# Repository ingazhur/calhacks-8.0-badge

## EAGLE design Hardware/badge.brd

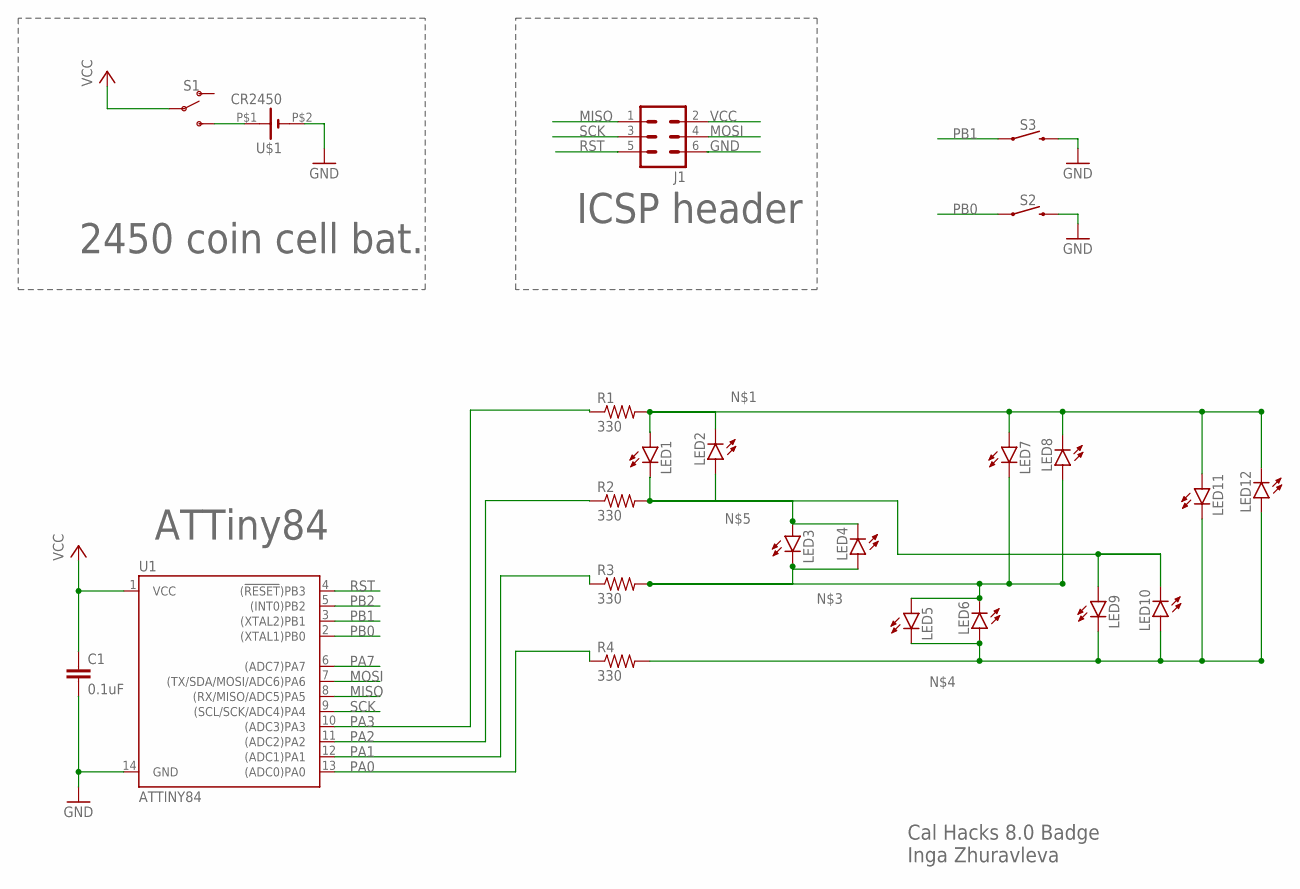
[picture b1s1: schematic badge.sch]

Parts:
C1: 0.1uF; C0603
J1: MA03-2
LED1, LED2, LED3, LED4, LED5, LED6, LED7, LED8, LED9, LED10, LED11, LED12: LED3MM
R1, R2, R3, R4: 330; R0805
S1: SWITCH-SPDT-PTH-11.6X4.0MM-KIT; SWITCH_SPDT_PTH_11.6X4.0MM_KIT
S2, S3: MOMENTARY-SWITCH-SPST-SMD-6.2MM-TALL; TACTILE_SWITCH_SMD_6.2MM_TALL
U1: ATTINY84; SO14
U$1: CR2450; BAT_2450_XL

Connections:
GND: C1.2, J1.6, S2.B2 (2), S3.B2 (2), U1.14 (GND), U$1.P$2 (-)
MISO: J1.1, U1.8 ((RX/MISO/ADC5)PA5)
MOSI: J1.4, U1.7 ((TX/SDA/MOSI/ADC6)PA6)
unnamed: LED1.A, LED2.K (C), LED7.A, LED8.K (C), LED11.A, LED12.K (C), R1.2
unnamed: S1.3 (S), U$1.P$1 (+)
unnamed: LED3.K (C), LED4.A, LED5.A, LED6.K (C), LED7.K (C), LED8.A, R3.2
unnamed: LED5.K (C), LED6.A, LED9.K (C), LED10.A, LED11.K (C), LED12.A, R4.2
unnamed: LED1.K (C), LED2.A, LED3.A, LED4.K (C), LED9.A, LED10.K (C), R2.2
PA0: R4.1, U1.13 ((ADC0)PA0)
PA1: R3.1, U1.12 ((ADC1)PA1)
PA2: R2.1, U1.11 ((ADC2)PA2)
PA3: R1.1, U1.10 ((ADC3)PA3)
PA7: U1.6 ((ADC7)PA7)
PB0: S2.A2 (1), U1.2 ((XTAL1)PB0)
PB1: S3.A2 (1), U1.3 ((XTAL2)PB1)
PB2: U1.5 ((INT0)PB2)
RST: J1.5, U1.4 ((!RESET!)PB3)
SCK: J1.3, U1.9 ((SCL/SCK/ADC4)PA4)
VCC: C1.1, J1.2, S1.2, U1.1 (VCC)

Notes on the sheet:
ATTiny84
2450 coin cell bat.
ICSP header
Cal Hacks 8.0 Badge Inga Zhuravleva

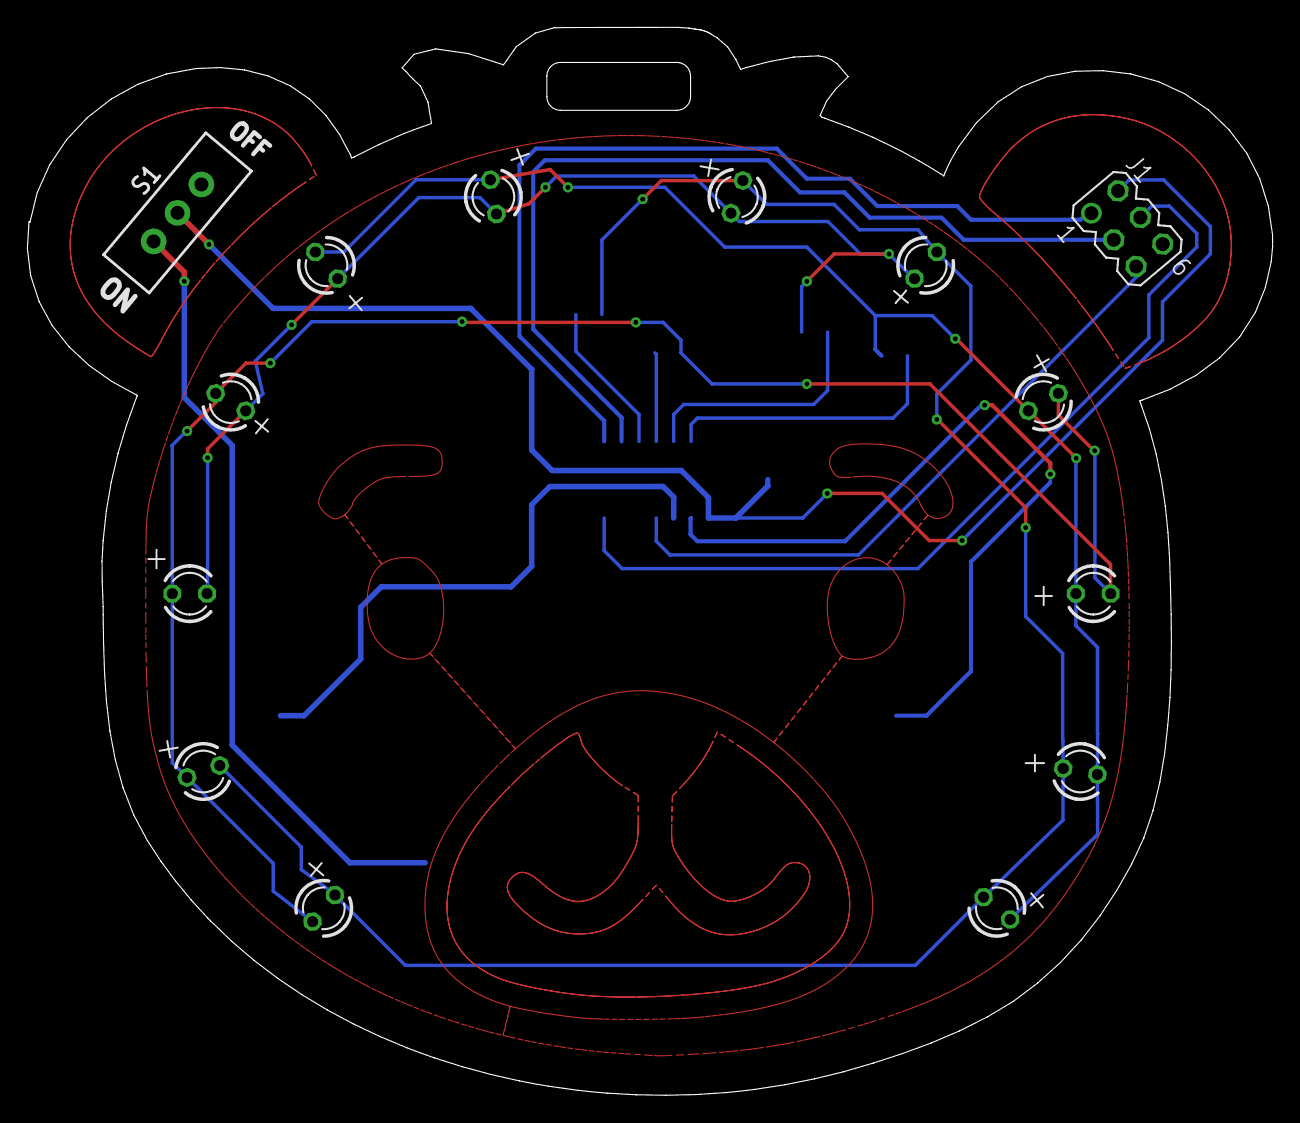
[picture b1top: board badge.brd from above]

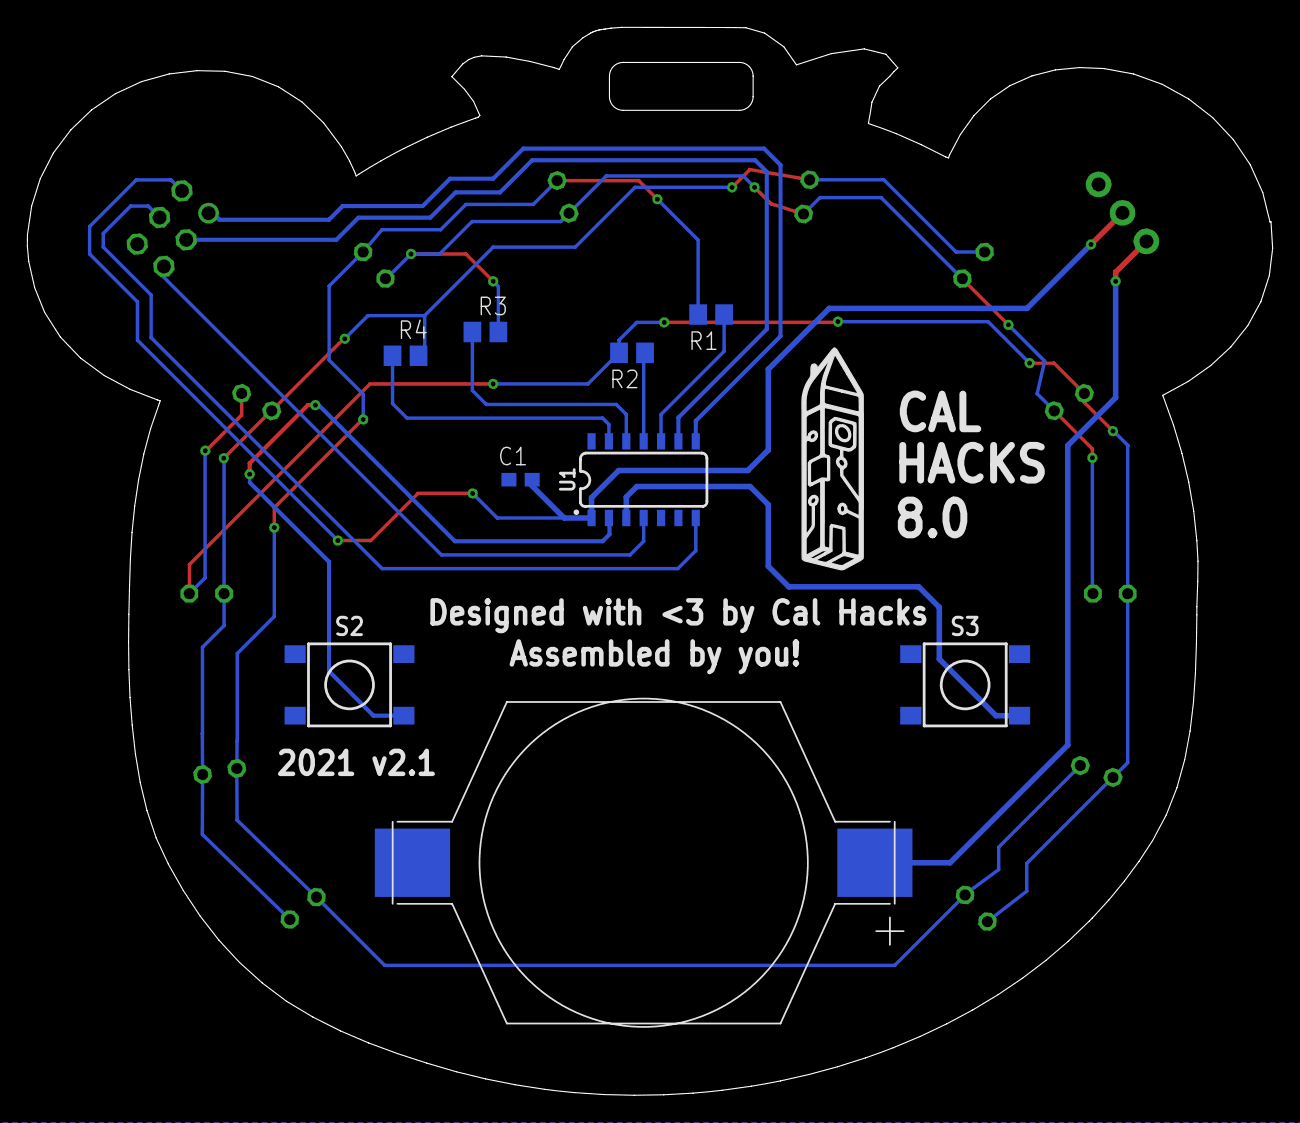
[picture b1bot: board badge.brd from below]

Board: 2 copper layers, 90.9 x 78.0 mm, 23 parts (9 on the bottom side), 17 nets.

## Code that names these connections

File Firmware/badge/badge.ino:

#define A 3 // pin 10 = PA3
#define B 2 // pin 11 = PA2
#define C 1 // pin 12 = PA1
#define D 0 // pin 13 = PA0

#define PIN_CONFIG 0
#define PIN_STATE 1

#define LED_Num 12

int led = 1;

int matrix[LED_Num][2][4] = {
  //           PIN_CONFIG                  PIN_STATE
  //    A       B       C      D         A     B    C    D
  { { OUTPUT, INPUT, INPUT, OUTPUT }, { HIGH, LOW, LOW, LOW } }, // 12
  { { INPUT, INPUT, OUTPUT, OUTPUT }, { LOW, LOW, LOW, HIGH } }, // 1
  { { INPUT, INPUT, OUTPUT, OUTPUT }, { LOW, LOW, HIGH, LOW } }, // 2
  { { INPUT, OUTPUT, OUTPUT, INPUT }, { LOW, LOW, HIGH, LOW } }, // ...
  { { INPUT, OUTPUT, OUTPUT, INPUT }, { LOW, HIGH, LOW, LOW } },
  { { OUTPUT, OUTPUT, INPUT, INPUT }, { LOW, HIGH, LOW, LOW } }, 
  { { OUTPUT, OUTPUT, INPUT, INPUT }, { HIGH, LOW, LOW, LOW } }, 
  { { INPUT, OUTPUT, INPUT, OUTPUT }, { LOW, LOW, LOW, HIGH } }, 
  { { INPUT, OUTPUT, INPUT, OUTPUT }, { LOW, HIGH, LOW, LOW } }, 
  { { OUTPUT, INPUT, OUTPUT, INPUT }, { LOW, LOW, HIGH, LOW } }, 
  { { OUTPUT, INPUT, OUTPUT, INPUT }, { HIGH, LOW, LOW, LOW } }, 
  { { OUTPUT, INPUT, INPUT, OUTPUT }, { LOW, LOW, LOW, HIGH } }  // 11
};

volatile byte state = LOW;

void setup() {
}

void loop() {
  random_blink();
}

void lightOn(int led) {
  pinMode( A, matrix[led][PIN_CONFIG][0] );
  pinMode( B, matrix[led][PIN_CONFIG][1] );
  pinMode( C, matrix[led][PIN_CONFIG][2] );
  pinMode( D, matrix[led][PIN_CONFIG][3] );
  digitalWrite( A, matrix[led][PIN_STATE][0] );
  digitalWrite( B, matrix[led][PIN_STATE][1] );
  digitalWrite( C, matrix[led][PIN_STATE][2] );
  digitalWrite( D, matrix[led][PIN_STATE][3] );
}

void random_blink() {
  while(1) {
    int led = random(0, LED_Num);
    lightOn(led);
    delay(10);
  }
}

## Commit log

2022-05-29 Uploading PCB and firmware files from 8.0 iteration

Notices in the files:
parts and their libraries:
SparkFun-Switches: Licensing: Creative Commons ShareAlike 4.0 International - https://creativecommons.org/licenses/by-sa/4.0
